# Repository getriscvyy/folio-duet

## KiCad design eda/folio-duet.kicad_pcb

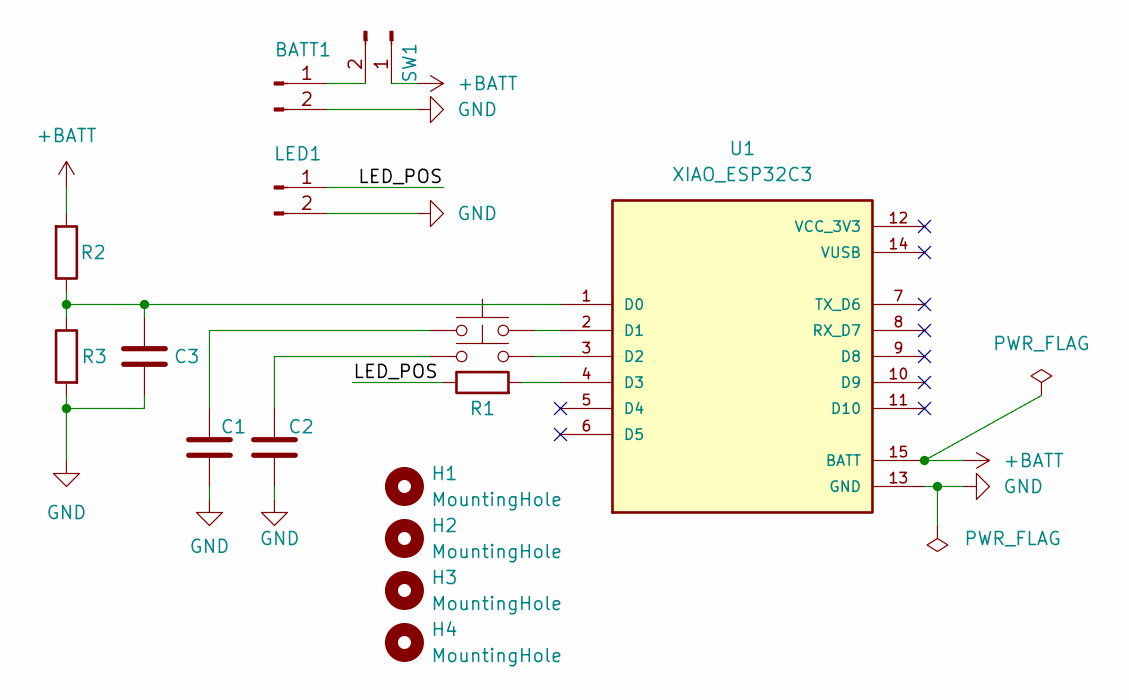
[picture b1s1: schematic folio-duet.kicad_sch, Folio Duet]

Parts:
BATT1: Conn_01x02_Pin; JST_XH_B2B-XH-A_1x02_P2.50mm_Vertical
C1, C2, C3: C; C_Disc_D3.0mm_W1.6mm_P2.50mm
H1, H2, H3, H4: MountingHole; MountingHole_2.2mm_M2
LED1: Conn_01x02_Pin; JST_XH_B2B-XH-A_1x02_P2.50mm_Vertical
PED_L1: SW_Push; SW_MX_THT
PED_R1: SW_Push; SW_MX_THT
R1: R1; R_Axial_DIN0204_L3.6mm_D1.6mm_P5.08mm_Horizontal
R2, R3: R; R_Axial_DIN0204_L3.6mm_D1.6mm_P5.08mm_Horizontal
SW1: Conn_01x02_Pin; JST_XH_B2B-XH-A_1x02_P2.50mm_Vertical
U1: XIAO_ESP32C3; MODULE_XIAO_ESP32C3; PARTREV 23/05/2022

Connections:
+BATT: R2.2, SW1.1, U1.15 (BATT)
/LED_POS: LED1.1, R1.1
GND: BATT1.2, C1.2, C2.2, C3.2, LED1.2, R3.2, U1.13 (GND)
unnamed: BATT1.1, SW1.2
unnamed: C1.1, PED_L1.2
unnamed: C2.1, PED_R1.1
unnamed: C3.1, R2.1, R3.1, U1.1 (D0)
unnamed: PED_L1.1, U1.2 (D1)
unnamed: PED_R1.2, U1.3 (D2)
unnamed: R1.2, U1.4 (D3)

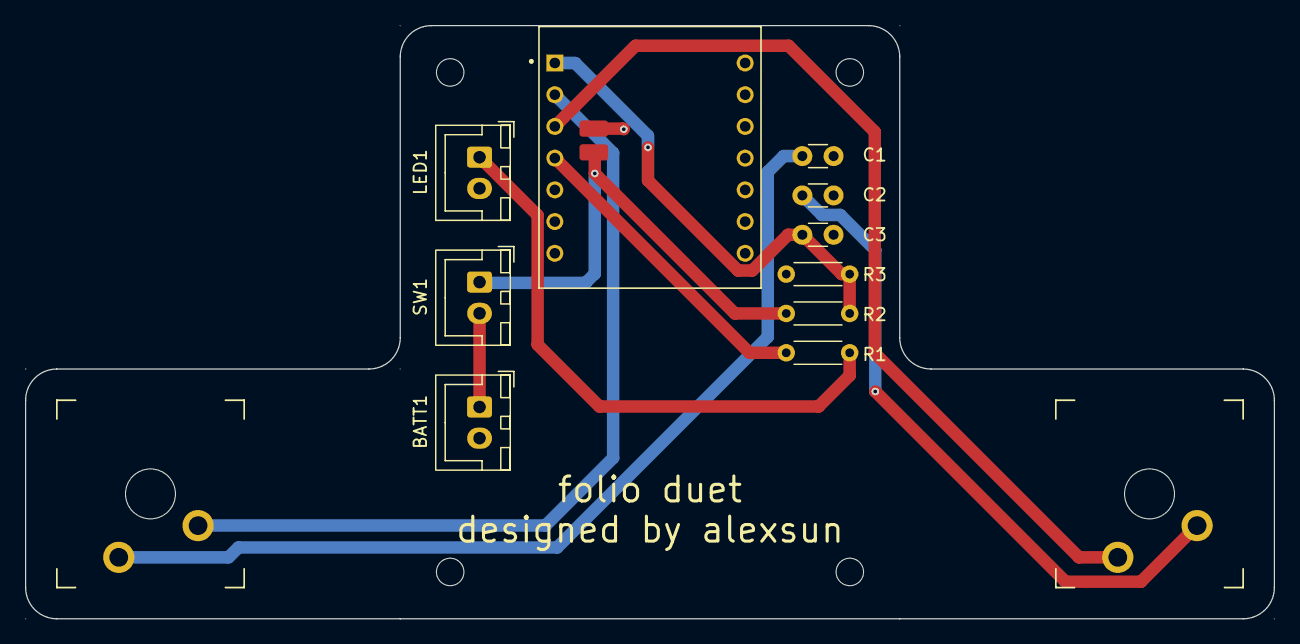
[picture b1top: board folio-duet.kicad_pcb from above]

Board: 2 copper layers, 100.0 x 47.5 mm, 16 parts (0 on the bottom side), 10 nets.

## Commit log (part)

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2026-05-26 Upload entire project
